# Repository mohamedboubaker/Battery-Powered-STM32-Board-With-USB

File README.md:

# Battery-Powered-STM32-Board-With-USB
An STM32 board that runs on a battery with MCP73831 and is easily programmable with USB thanks to the CP2102 USB-to-UART chip. 

Project Documentation: https://embeddedprojects101.com/design-a-battery-powered-stm32-board-with-usb/

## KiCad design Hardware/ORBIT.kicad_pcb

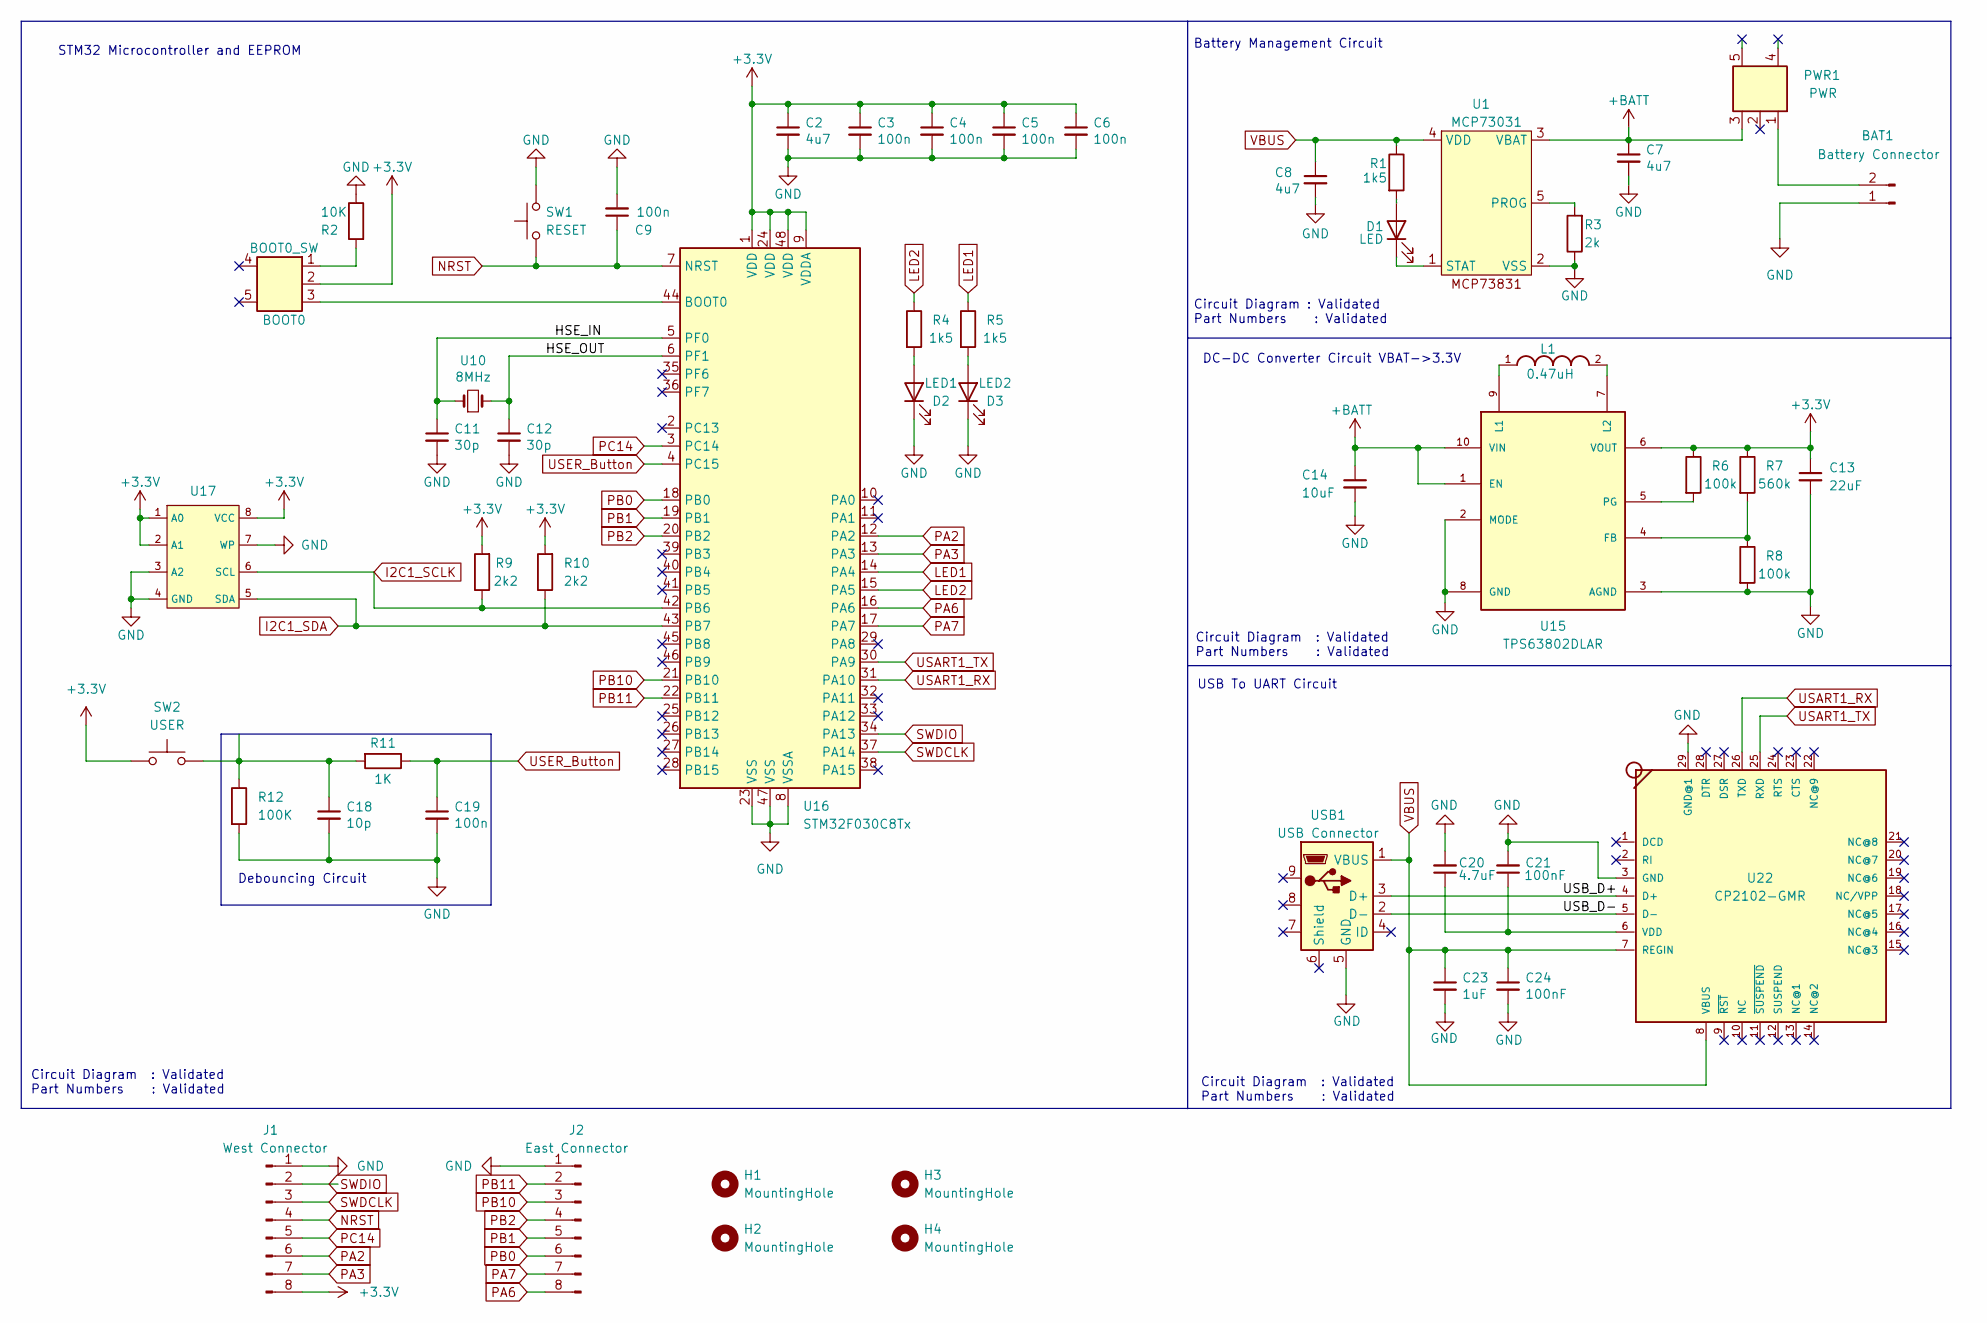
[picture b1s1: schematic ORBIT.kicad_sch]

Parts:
BAT1: Battery Connector; JST_PH_B2B-PH-SM4-TB_1x02-1MP_P2.00mm_Vertical; LCSC Part # C160352
BOOT0: BOOT0_SW; K3-1270L-F1; LCSC Part # C145857
C2, C7, C8: 4u7; C_0603_1608Metric; LCSC Part # C19666
C3, C4, C5, C6, C9, C19: 100n; C_0603_1608Metric; LCSC Part # C14663
C11, C12: 30p; C_0603_1608Metric; LCSC Part # C1658
C13: 22uF; C_0603_1608Metric; LCSC Part # C59461
C14: 10uF; C_0603_1608Metric; LCSC Part # C19702
C18: 10p; C_0603_1608Metric; LCSC Part # C1634
C20: 4.7uF; C_0603_1608Metric; LCSC Part # C19666
C21, C24: 100nF; C_0603_1608Metric; LCSC Part # C14663
C23: 1uF; C_0603_1608Metric; LCSC Part # C15849
D1: LED; LED_0603_1608Metric; LCSC Part # C72043
D2: LED1; LED_0603_1608Metric; LCSC Part # C72043
D3: LED2; LED_0603_1608Metric; LCSC Part # C72041
H1, H2, H4: MountingHole; MountingHole_2.5mm_Pad_Via
H3: MountingHole; MountingHole_2.2mm_M2_Pad_Via
J1: West Connector; PinHeader_1x08_P2.54mm_Vertical
J2: East Connector; PinHeader_1x08_P2.54mm_Vertical
L1: 0.47uH; INDC2016X120N; LCSC Part # C668312
PWR1: PWR; K3-1270L-F1; LCSC Part # C145857
R1, R4, R5: 1k5; R_0603_1608Metric; LCSC Part # C22843
R2: 10K; R_0603_1608Metric; LCSC Part # C25804
R3: 2k; R_0603_1608Metric; LCSC Part # C22975
R6, R8: 100k; R_0603_1608Metric; LCSC Part # C25803
R7: 560k; R_0603_1608Metric; LCSC Part # C101109
R9, R10: 2k2; R_0603_1608Metric; LCSC Part # C4190
R11: 1K; R_0603_1608Metric; LCSC Part # C21190
R12: 100K; R_0603_1608Metric; LCSC Part # C25803
SW1: RESET; SW_Push_1P1T_NO_CK_KSC6xxJ; LCSC Part # C318884
SW2: USER; SW_Push_1P1T_NO_CK_KSC6xxJ; LCSC Part # C318884
U1: MCP73031; SOT-23-5; LCSC Part # C424093
U10: 8MHz; Crystal_SMD_5032-2Pin_5.0x3.2mm; LCSC Part # C115962
U15: TPS63802DLAR; LCSC Part # C2845237
U16: STM32F030C8Tx; LQFP-48_7x7mm_P0.5mm; LCSC Part # C23922
U17: SOIC127P600X175-8N
U22: CP2102-GMR; QFN28G_0.5-5X5MM; LCSC Part# C6568
USB1: USB Connector; MINI-USB-SMD_MINI-5PTP; LCSC Part # C2681563

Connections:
+3.3V: BOOT0.2, C2.1, C3.1, C4.1, C5.1, C6.1, C13.1, J1.8, R6.1, R7.1, R9.2, R10.2, SW2.1, U15.6 (VOUT), U16.1 (VDD), U16.9 (VDDA), U16.24 (VDD), U16.48 (VDD), U17.1 (A0), U17.2 (A1), U17.8 (VCC)
+BATT: C7.1, C14.1, PWR1.3, U1.3 (VBAT), U15.1 (EN), U15.10 (VIN)
/HSE_IN: C11.1, U10.1, U16.5 (PF0)
/HSE_OUT: C12.1, U10.2, U16.6 (PF1)
/USB_D+: U22.4 (D+), USB1.3 (D+)
/USB_D-: U22.5 (D-), USB1.2 (D-)
GND: BAT1.1, C2.2, C3.2, C4.2, C5.2, C6.2, C7.2, C8.2, C9.2, C11.2, C12.2, C13.2, C14.2, C18.2, C19.2, C20.2, C21.2, C23.2, C24.2, D2.1 (K), D3.1 (K), J1.1, J2.1, R2.1, R3.1, R8.2, R12.2, SW1.2, U1.2 (VSS), U15.2 (MODE), U15.3 (AGND), U15.8 (GND), U16.8 (VSSA), U16.23 (VSS), U16.47 (VSS), U17.3 (A2), U17.4 (GND), U17.7 (WP), U22.3 (GND), U22.29 (GND@1), USB1.5 (GND)
I2C1_SCLK: R9.1, U16.42 (PB6), U17.6 (SCL)
I2C1_SDA: R10.1, U16.43 (PB7), U17.5 (SDA)
LED1: R5.1, U16.14 (PA4)
LED2: R4.1, U16.15 (PA5)
NRST: C9.1, J1.4, SW1.1, U16.7 (NRST)
unnamed: BAT1.2, PWR1.1
unnamed: BOOT0.1, R2.2
unnamed: C18.1, R11.2, R12.1, SW2.2
unnamed: D1.2 (A), R1.2
unnamed: D1.1 (K), U1.1 (STAT)
unnamed: D2.2 (A), R4.2
unnamed: D3.2 (A), R5.2
unnamed: R3.2, U1.5 (PROG)
unnamed: R7.2, R8.1, U15.4 (FB)
unnamed: L1.1, U15.9 (L1)
unnamed: L1.2, U15.7 (L2)
unnamed: R6.2, U15.5 (PG)
unnamed: BOOT0.3, U16.44 (BOOT0)
unnamed: C20.1, C21.1, U22.6 (VDD)
PA2: J1.6, U16.12 (PA2)
PA3: J1.7, U16.13 (PA3)
PA6: J2.8, U16.16 (PA6)
PA7: J2.7, U16.17 (PA7)
PB0: J2.6, U16.18 (PB0)
PB1: J2.5, U16.19 (PB1)
PB2: J2.4, U16.20 (PB2)
PB10: J2.3, U16.21 (PB10)
PB11: J2.2, U16.22 (PB11)
PC14: J1.5, U16.3 (PC14)
SWDCLK: J1.3, U16.37 (PA14)
SWDIO: J1.2, U16.34 (PA13)
USART1_RX: U16.31 (PA10), U22.26 (TXD)
USART1_TX: U16.30 (PA9), U22.25 (RXD)
USER_Button: C19.1, R11.1, U16.4 (PC15)
VBUS: C8.1, C23.1, C24.1, R1.1, U1.4 (VDD), U22.7 (REGIN), U22.8 (VBUS), USB1.1 (VBUS)

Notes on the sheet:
Circuit Diagram : Validated Part Numbers : Validated
Battery Management Circuit
USB To UART Circuit
Debouncing Circuit
STM32 Microcontroller and EEPROM
Circuit Diagram : Validated Part Numbers : Validated
DC-DC Converter Circuit VBAT->3.3V

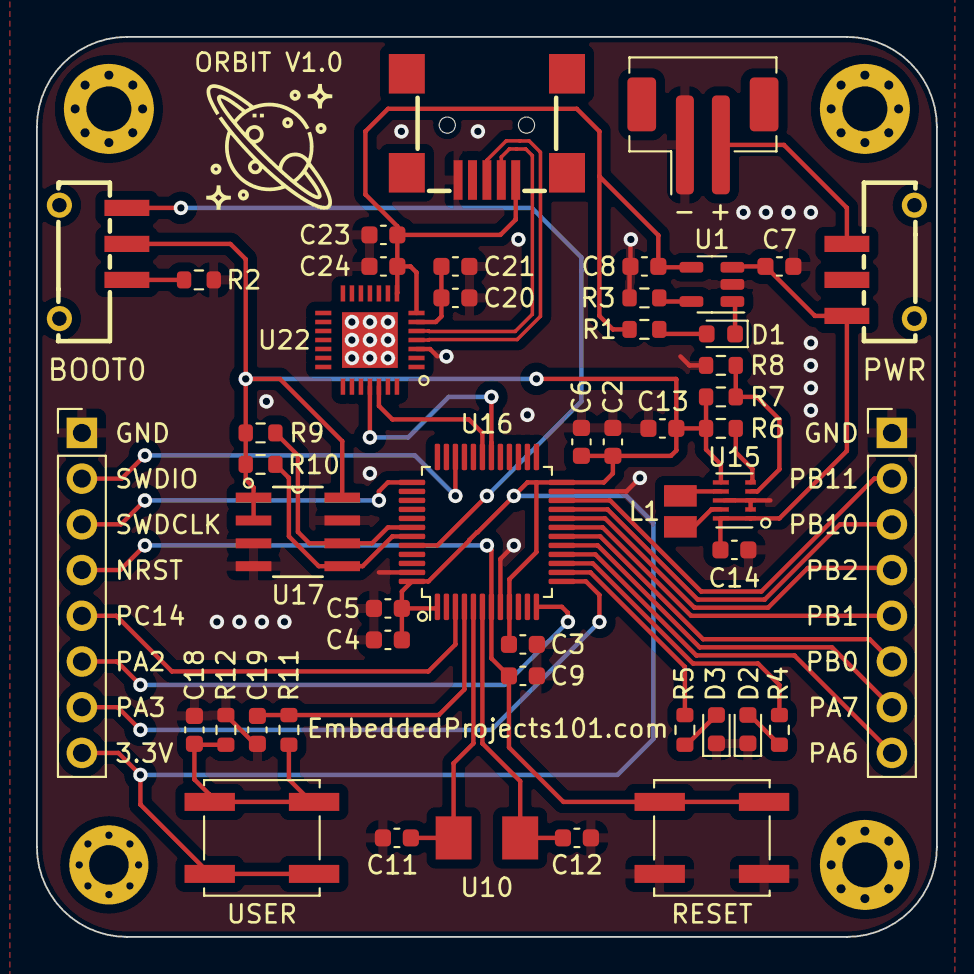
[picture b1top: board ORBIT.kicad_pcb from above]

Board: 2 copper layers, 50.0 x 50.0 mm, 53 parts (0 on the bottom side), 42 nets.

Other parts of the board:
O: LOGO

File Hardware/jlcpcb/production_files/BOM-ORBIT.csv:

Comment,Designator,Footprint,LCSC
560k,R7,R_0603_1608Metric,C101109
8MHz,U10,Crystal_SMD_5032-2Pin_5.0x3.2mm,C115962
BOOT0_SW,"BOOT0,PWR1",K3-1270L-F1,C145857
100n,"C19,C21,C24,C3,C4,C5,C6,C9",C_0603_1608Metric,C14663
1uF,C23,C_0603_1608Metric,C15849
Battery Connector,BAT1,JST_PH_B2B-PH-SM4-TB_1x02-1MP_P2.00mm_Vertical,C160352
10p,C18,C_0603_1608Metric,C1634
30p,"C11,C12",C_0603_1608Metric,C1658
4u7,"C2,C20,C7,C8",C_0603_1608Metric,C19666
10uF,C14,C_0603_1608Metric,C19702
1K,R11,R_0603_1608Metric,C21190
1k5,"R1,R4,R5",R_0603_1608Metric,C22843
2k,R3,R_0603_1608Metric,C22975
STM32F030C8Tx,U16,LQFP-48_7x7mm_P0.5mm,C23922
100K,"R12,R6,R8",R_0603_1608Metric,C25803
10K,R2,R_0603_1608Metric,C25804
USB Connector,USB1,MINI-USB-SMD_MINI-5PTP,C2681563
TPS63802DLAR,U15,TPS63802DLAR,C2845237
RESET,"SW1,SW2",SW_Push_1P1T_NO_CK_KSC6xxJ,C318884
2k2,"R10,R9",R_0603_1608Metric,C4190
MCP73031,U1,SOT-23-5,C424093
22uF,C13,C_0603_1608Metric,C59461
AT24C128C,U17,SOIC127P600X175-8N,C6478
CP2102-GMR,U22,QFN28G_0.5-5X5MM,C6568
0.47uH,L1,INDC2016X120N,C668312
LED2,D3,LED_0603_1608Metric,C72041
LED,"D1,D2",LED_0603_1608Metric,C72043
East Connector,J2,PinHeader_1x08_P2.54mm_Vertical,
MountingHole,H2,MountingHole_2.5mm_Pad_Via,
MountingHole,H1,MountingHole_2.5mm_Pad_Via,
MountingHole,H4,MountingHole_2.5mm_Pad_Via,
MountingHole,H3,MountingHole_2.2mm_M2_Pad_Via,
West Connector,J1,PinHeader_1x08_P2.54mm_Vertical,

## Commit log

2023-12-21 Added .gitignore
2023-12-21 added ignored files
2023-12-21 Version 1.0
2023-12-21 Version V1.0
2023-12-21 all components in the final positioned
2023-12-21 V 1.0
2023-12-21 Add legend
